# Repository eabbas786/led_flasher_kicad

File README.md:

# LED Flasher Designed on KiCad

## Schematic

## PCB Layout

## Layout in 3D Viewer

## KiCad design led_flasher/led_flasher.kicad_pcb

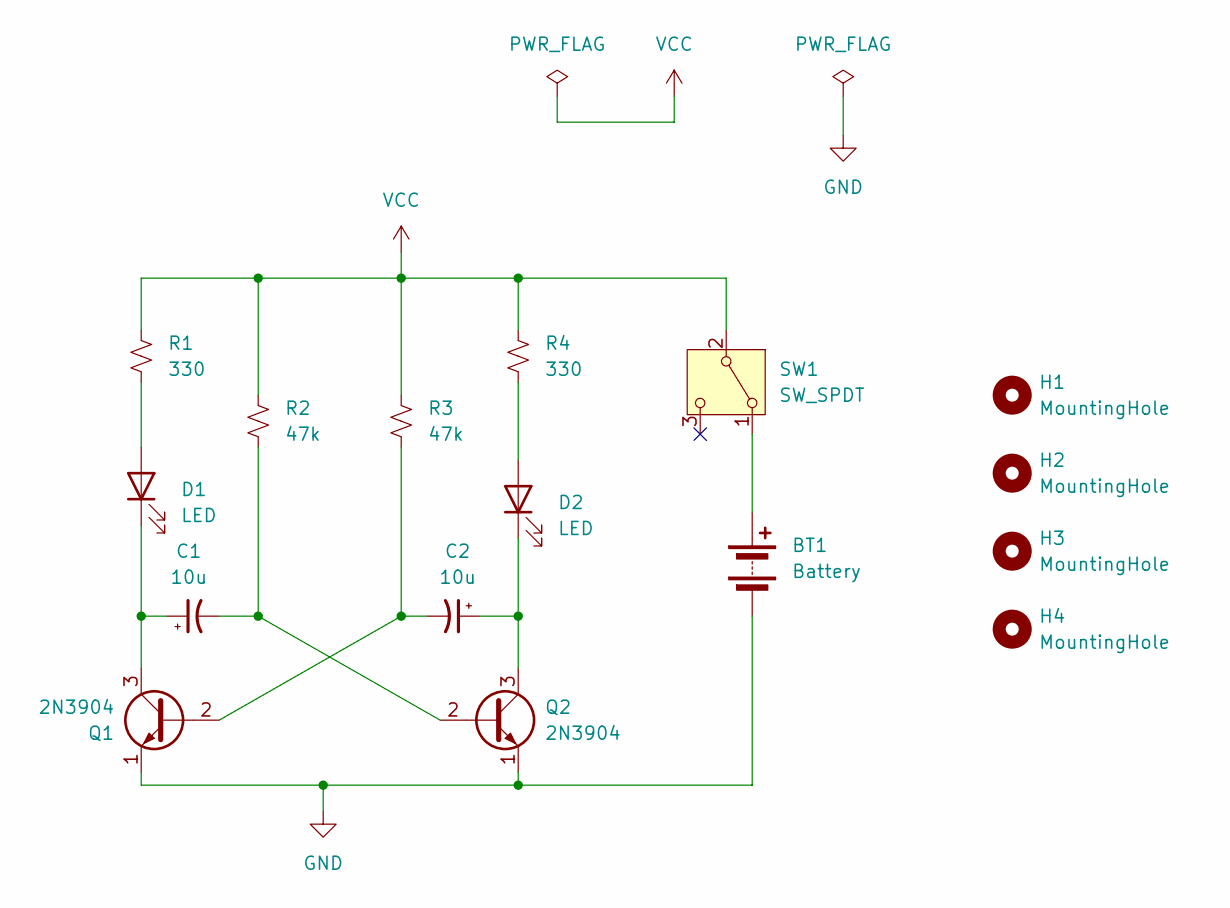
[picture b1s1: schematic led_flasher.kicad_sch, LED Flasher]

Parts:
BT1: Battery; BatteryHolder_Keystone_2479_3xAAA
C1, C2: 10u; CP_Radial_D6.3mm_P2.50mm
D1, D2: LED; LED_D5.0mm
H1, H2, H3, H4: MountingHole; MountingHole_3.2mm_M3
Q1, Q2: 2N3904; TO-92_Inline
R1, R4: 330; R_Axial_DIN0207_L6.3mm_D2.5mm_P10.16mm_Horizontal
R2, R3: 47k; R_Axial_DIN0207_L6.3mm_D2.5mm_P10.16mm_Horizontal
SW1: SW_SPDT; SW_E-Switch_EG1224_SPDT_Angled

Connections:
GND: BT1.2 (-), Q1.1 (E), Q2.1 (E)
unnamed: BT1.1 (+), SW1.1 (A)
unnamed: D1.2 (A), R1.2
unnamed: C1.1, D1.1 (K), Q1.3 (C)
unnamed: D2.2 (A), R4.2
unnamed: C2.1, D2.1 (K), Q2.3 (C)
unnamed: C2.2, Q1.2 (B), R3.2
unnamed: C1.2, Q2.2 (B), R2.2
VCC: R1.1, R2.1, R3.1, R4.1, SW1.2 (B)

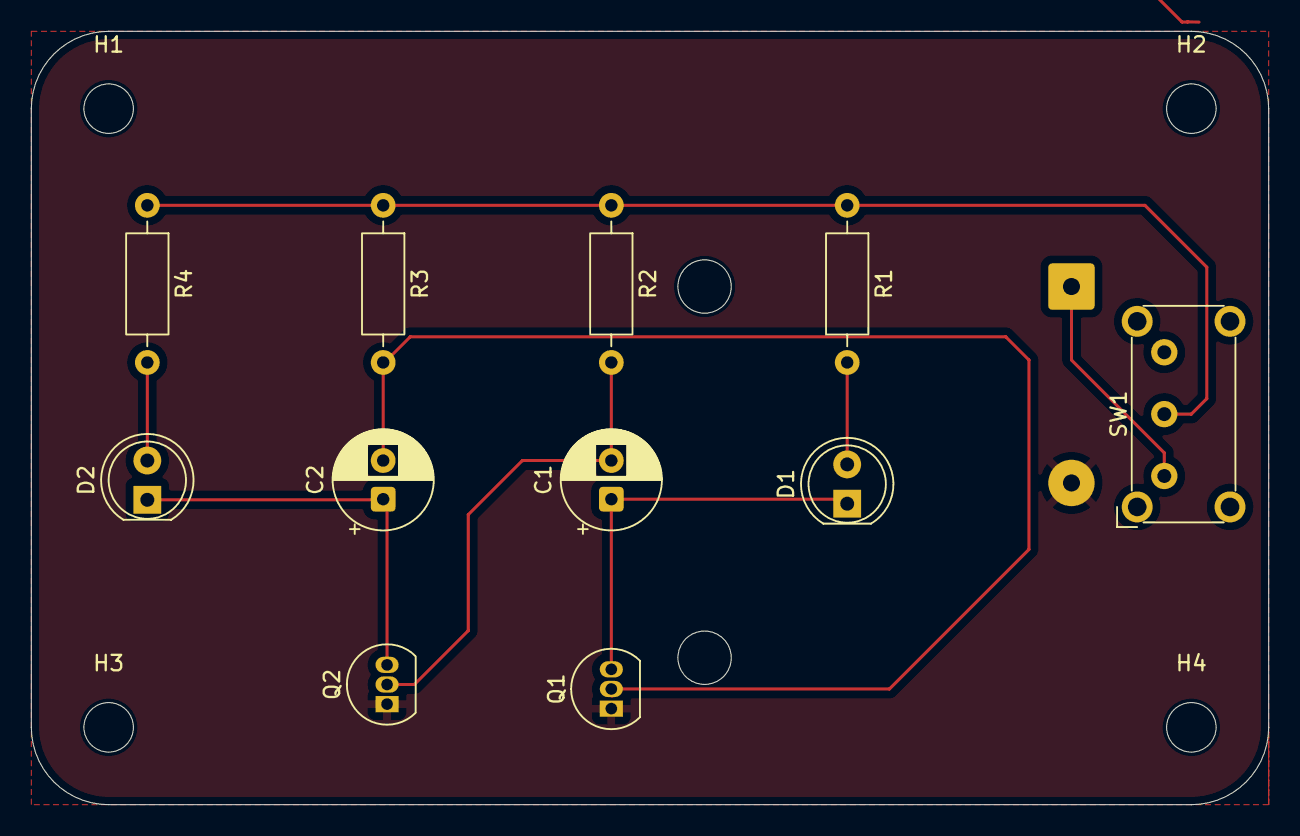
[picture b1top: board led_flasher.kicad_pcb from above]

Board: 2 copper layers, 80.0 x 50.0 mm, 16 parts (1 on the bottom side), 9 nets.

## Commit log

2026-01-13 Add picture of PCB layout in 3D Viewer
